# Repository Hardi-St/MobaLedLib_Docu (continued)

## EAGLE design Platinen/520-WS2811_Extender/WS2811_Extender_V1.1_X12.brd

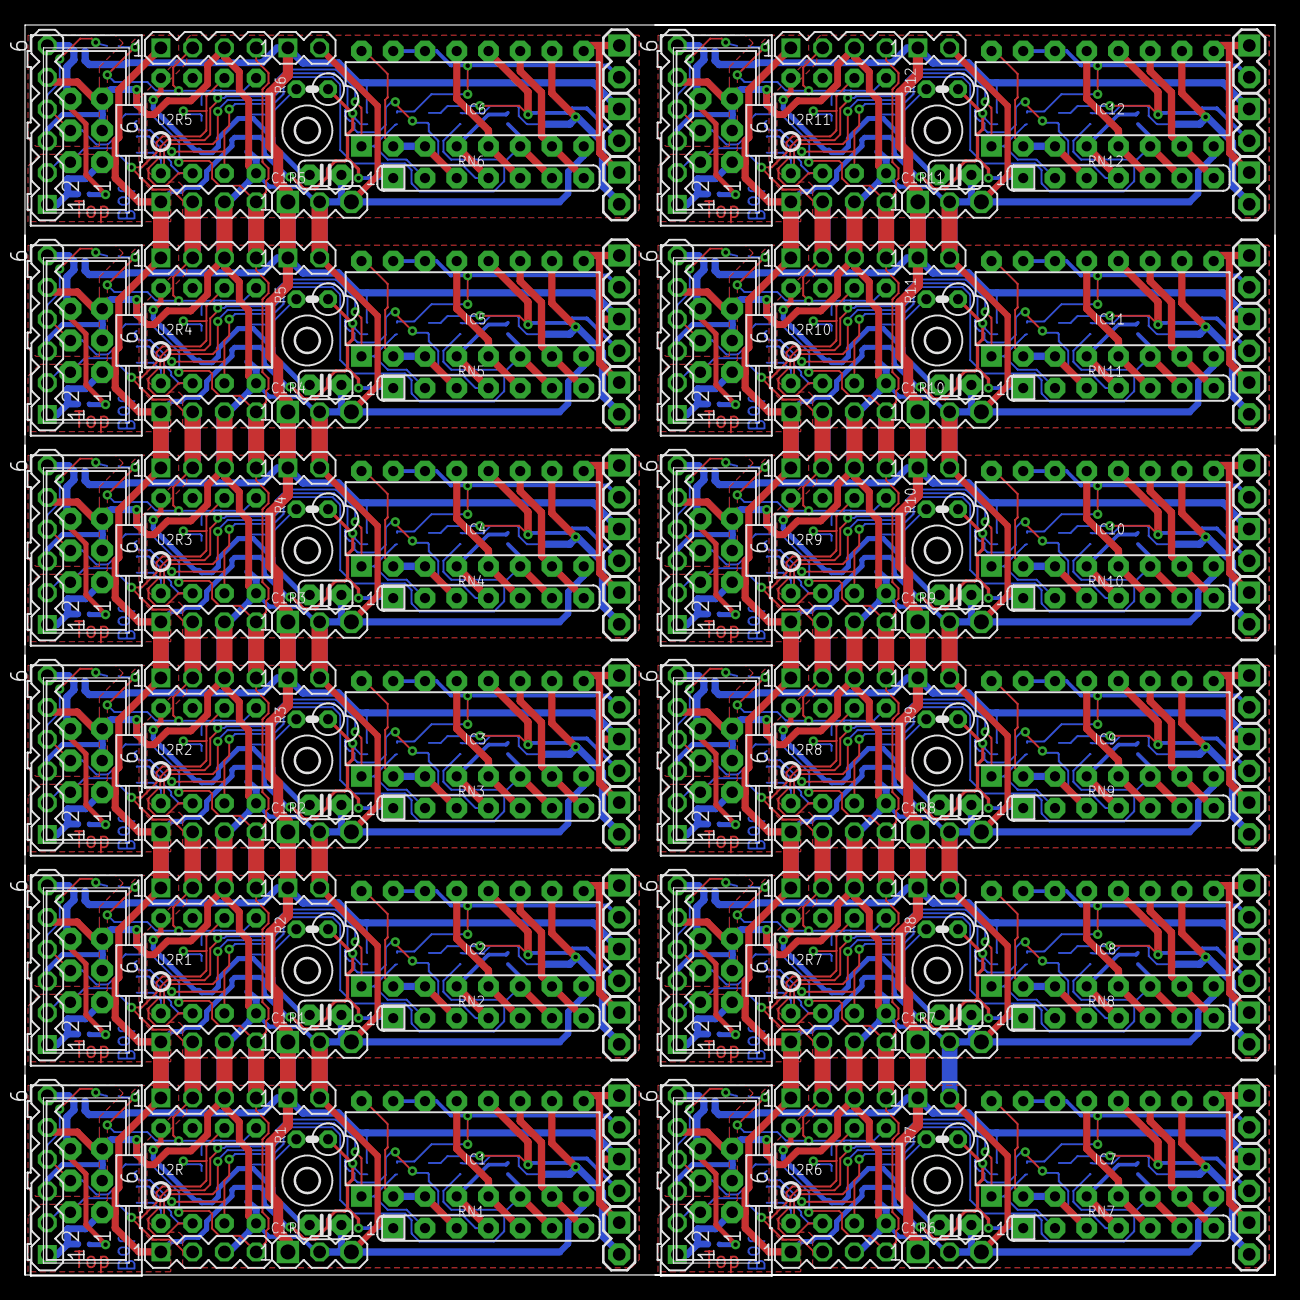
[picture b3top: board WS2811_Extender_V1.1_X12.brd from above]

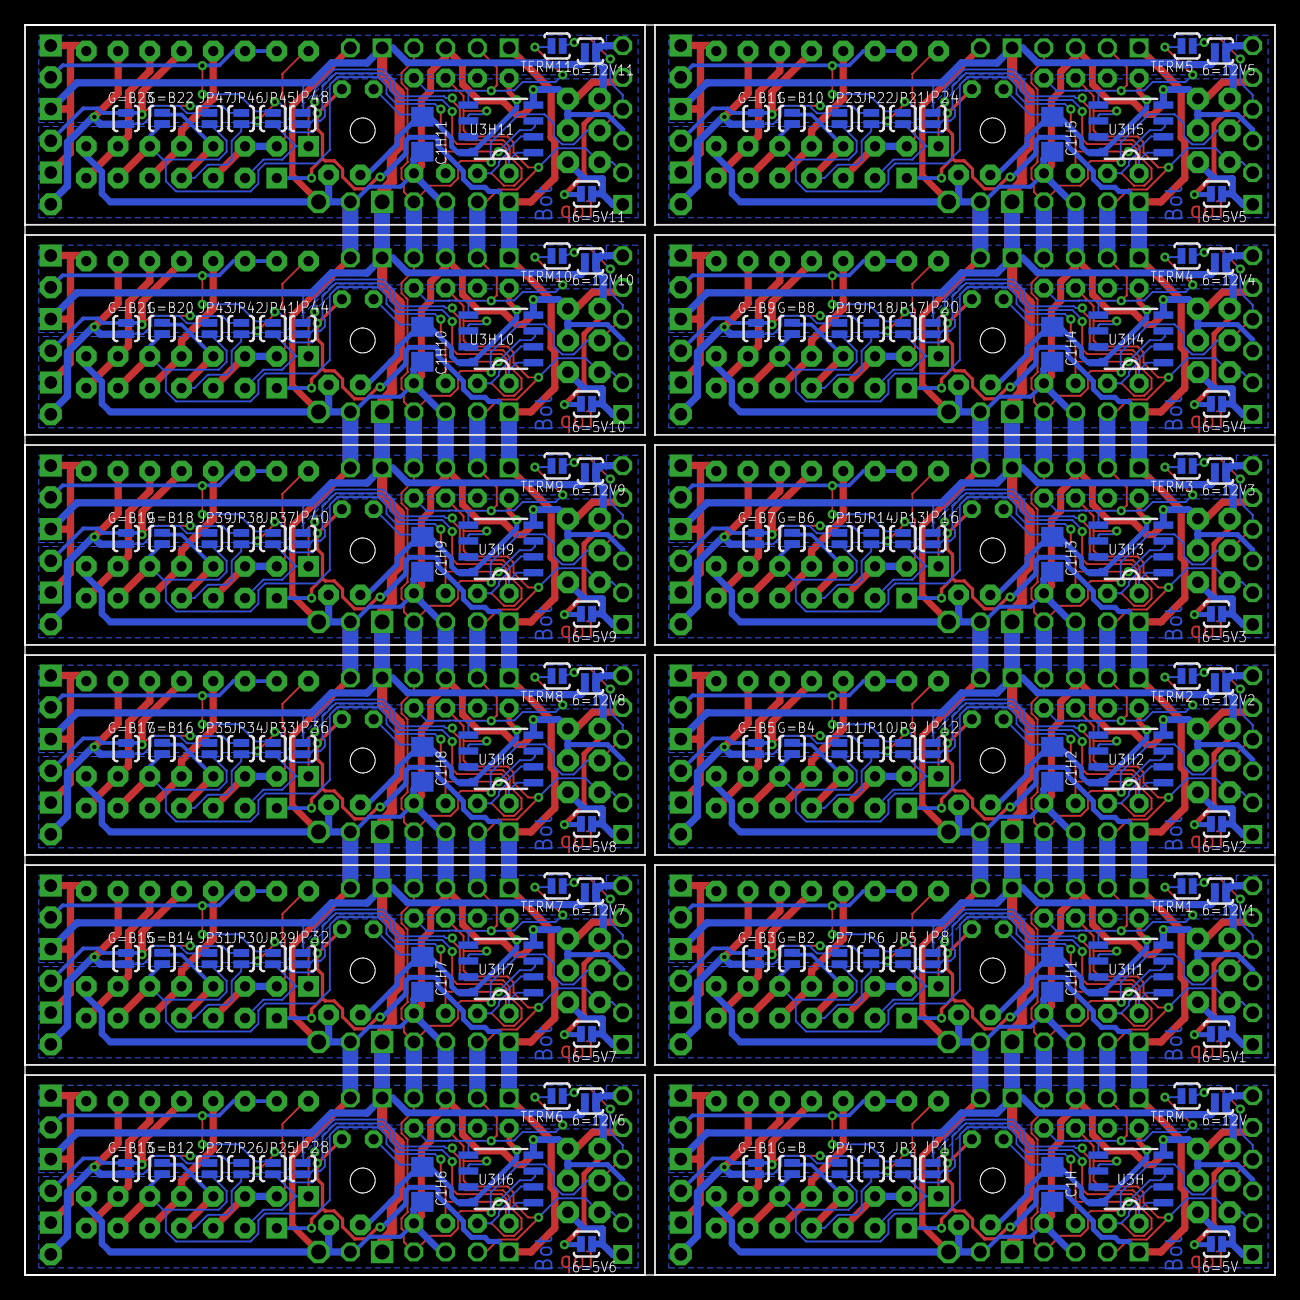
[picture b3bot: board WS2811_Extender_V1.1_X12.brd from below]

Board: 2 copper layers, 100.0 x 100.0 mm, 312 parts (132 on the bottom side), 204 nets.

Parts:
6=5V, 6=5V1, 6=5V2, 6=5V3, 6=5V4, 6=5V5, 6=5V6, 6=5V7, 6=5V8, 6=5V9, 6=5V10, 6=5V11, 6=12V, 6=12V1, 6=12V2, 6=12V3, 6=12V4, 6=12V5, 6=12V6, 6=12V7, 6=12V8, 6=12V9, 6=12V10, 6=12V11: SOLDERJUMPERNO; SJ_2S-NO
C1H, C1H1, C1H2, C1H3, C1H4, C1H5, C1H6, C1H7, C1H8, C1H9, C1H10, C1H11: 100n; C1206
C1R, C1R1, C1R2, C1R3, C1R4, C1R5, C1R6, C1R7, C1R8, C1R9, C1R10, C1R11: 100n; C025-024X044
G=B, G=B1, G=B2, G=B3, G=B4, G=B5, G=B6, G=B7, G=B8, G=B9, G=B10, G=B11, G=B12, G=B13, G=B14, G=B15, G=B16, G=B17, G=B18, G=B19, G=B20, G=B21, G=B22, G=B23: SOLDERJUMPERNO; SJ_2S-NO
H1, H2, H3, H4, H5, H6, H7, H8, H9, H10, H11, H12: MOUNT-HOLE2.0; 2,0
IC1, IC2, IC3, IC4, IC5, IC6, IC7, IC8, IC9, IC10, IC11, IC12: ULN2003AN; DIL16
J1, J5, J8, J11, J14, J17, J20, J23, J26, J29, J32, J35: Out2; 1X02
J2, J6, J9, J12, J15, J18, J21, J24, J27, J30, J33, J36: Out3; 1X02
J3, J4, J7, J10, J13, J16, J19, J22, J25, J28, J31, J34: Out1; 1X02
JP1, JP2, JP3, JP4, JP5, JP6, JP7, JP8, JP9, JP10, JP11, JP12, JP13, JP14, JP15, JP16, JP17, JP18, JP19, JP20, JP21, JP22, JP23, JP24, JP25, JP26, JP27, JP28, JP29, JP30, JP31, JP32, JP33, JP34, JP35, JP36, JP37, JP38, JP39, JP40, JP41, JP42, JP43, JP44, JP45, JP46, JP47, JP48: SOLDERJUMPERNO; SJ_2S-NO
O1, O2, O3, O4, O5, O6, O7, O8, O9, O10, O11, O12: ML6
R1, R2, R3, R4, R5, R6, R7, R8, R9, R10, R11, R12: 150; RCL_0207/2V
RN1, RN2, RN3, RN4, RN5, RN6, RN7, RN8, RN9, RN10, RN11, RN12: 1K; SIL7
SV1, SV8, SV13, SV18, SV23, SV28, SV33, SV38, SV43, SV48, SV53, SV58: MA02-1
SV2, SV10, SV15, SV20, SV25, SV30, SV35, SV40, SV45, SV50, SV55, SV60: MA06-1
SV3, SV4, SV5, SV7, SV11, SV12, SV16, SV17, SV21, SV22, SV26, SV27, SV31, SV32, SV36, SV37, SV41, SV42, SV46, SV47, SV51, SV52, SV56, SV57: MA04-1
SV6, SV9, SV14, SV19, SV24, SV29, SV34, SV39, SV44, SV49, SV54, SV59: MA03-1
TERM, TERM1, TERM2, TERM3, TERM4, TERM5, TERM6, TERM7, TERM8, TERM9, TERM10, TERM11: SOLDERJUMPERNO; SJ_2S-NO
U2R, U2R1, U2R2, U2R3, U2R4, U2R5, U2R6, U2R7, U2R8, U2R9, U2R10, U2R11: TINY45-20-DIP; S3PO_MODUL_WS2811_SOUND_MP3-TF-16P_WS2811_AND_ATTINY_WS2811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
U3H, U3H1, U3H2, U3H3, U3H4, U3H5, U3H6, U3H7, U3H8, U3H9, U3H10, U3H11: WS2811 SOT-8; SOP8

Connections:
12V: 6=12V.2, IC1.9, J1.1, J2.1, J4.1, JP1.2, SV1.1, SV6.1
12V1: 6=12V1.2, IC2.9, J3.1, J5.1, J6.1, JP8.2, SV8.1, SV9.1
12V2: 6=12V2.2, IC3.9, J7.1, J8.1, J9.1, JP12.2, SV13.1, SV14.1
12V3: 6=12V3.2, IC4.9, J10.1, J11.1, J12.1, JP16.2, SV18.1, SV19.1
12V4: 6=12V4.2, IC5.9, J13.1, J14.1, J15.1, JP20.2, SV23.1, SV24.1
12V5: 6=12V5.2, IC6.9, J16.1, J17.1, J18.1, JP24.2, SV28.1, SV29.1
12V6: 6=12V6.2, IC7.9, J19.1, J20.1, J21.1, JP28.2, SV33.1, SV34.1
12V7: 6=12V7.2, IC8.9, J22.1, J23.1, J24.1, JP32.2, SV38.1, SV39.1
12V8: 6=12V8.2, IC9.9, J25.1, J26.1, J27.1, JP36.2, SV43.1, SV44.1
12V9: 6=12V9.2, IC10.9, J28.1, J29.1, J30.1, JP40.2, SV48.1, SV49.1
12V10: 6=12V10.2, IC11.9, J31.1, J32.1, J33.1, JP44.2, SV53.1, SV54.1
12V11: 6=12V11.2, IC12.9, J34.1, J35.1, J36.1, JP48.2, SV58.1, SV59.1
+5V: 6=5V.2, JP1.1, O1.1, R1.1, RN1.1, SV2.1, SV3.1, SV4.1
+5V1: 6=5V1.2, JP8.1, O2.1, R2.1, RN2.1, SV5.1, SV7.1, SV10.1
+5V2: 6=5V2.2, JP12.1, O3.1, R3.1, RN3.1, SV11.1, SV12.1, SV15.1
+5V3: 6=5V3.2, JP16.1, O4.1, R4.1, RN4.1, SV16.1, SV17.1, SV20.1
+5V4: 6=5V4.2, JP20.1, O5.1, R5.1, RN5.1, SV21.1, SV22.1, SV25.1
+5V5: 6=5V5.2, JP24.1, O6.1, R6.1, RN6.1, SV26.1, SV27.1, SV30.1
+5V6: 6=5V6.2, JP28.1, O7.1, R7.1, RN7.1, SV31.1, SV32.1, SV35.1
+5V7: 6=5V7.2, JP32.1, O8.1, R8.1, RN8.1, SV36.1, SV37.1, SV40.1
+5V8: 6=5V8.2, JP36.1, O9.1, R9.1, RN9.1, SV41.1, SV42.1, SV45.1
+5V9: 6=5V9.2, JP40.1, O10.1, R10.1, RN10.1, SV46.1, SV47.1, SV50.1
+5V10: 6=5V10.2, JP44.1, O11.1, R11.1, RN11.1, SV51.1, SV52.1, SV55.1
+5V11: 6=5V11.2, JP48.1, O12.1, R12.1, RN12.1, SV56.1, SV57.1, SV60.1
GND: C1H.2, C1R.2, IC1.8, O1.3, O1.5, SV1.2, SV2.3, SV2.5, SV3.3, SV4.3, SV6.2, SV6.3, U2R.4, U3H.4
GND1: C1H1.2, C1R1.2, IC2.8, O2.3, O2.5, SV5.3, SV7.3, SV8.2, SV9.2, SV9.3, SV10.3, SV10.5, U2R1.4, U3H1.4
GND2: C1H2.2, C1R2.2, IC3.8, O3.3, O3.5, SV11.3, SV12.3, SV13.2, SV14.2, SV14.3, SV15.3, SV15.5, U2R2.4, U3H2.4
GND3: C1H3.2, C1R3.2, IC4.8, O4.3, O4.5, SV16.3, SV17.3, SV18.2, SV19.2, SV19.3, SV20.3, SV20.5, U2R3.4, U3H3.4
GND4: C1H4.2, C1R4.2, IC5.8, O5.3, O5.5, SV21.3, SV22.3, SV23.2, SV24.2, SV24.3, SV25.3, SV25.5, U2R4.4, U3H4.4
GND5: C1H5.2, C1R5.2, IC6.8, O6.3, O6.5, SV26.3, SV27.3, SV28.2, SV29.2, SV29.3, SV30.3, SV30.5, U2R5.4, U3H5.4
GND6: C1H6.2, C1R6.2, IC7.8, O7.3, O7.5, SV31.3, SV32.3, SV33.2, SV34.2, SV34.3, SV35.3, SV35.5, U2R6.4, U3H6.4
GND7: C1H7.2, C1R7.2, IC8.8, O8.3, O8.5, SV36.3, SV37.3, SV38.2, SV39.2, SV39.3, SV40.3, SV40.5, U2R7.4, U3H7.4
GND8: C1H8.2, C1R8.2, IC9.8, O9.3, O9.5, SV41.3, SV42.3, SV43.2, SV44.2, SV44.3, SV45.3, SV45.5, U2R8.4, U3H8.4
GND9: C1H9.2, C1R9.2, IC10.8, O10.3, O10.5, SV46.3, SV47.3, SV48.2, SV49.2, SV49.3, SV50.3, SV50.5, U2R9.4, U3H9.4
GND10: C1H10.2, C1R10.2, IC11.8, O11.3, O11.5, SV51.3, SV52.3, SV53.2, SV54.2, SV54.3, SV55.3, SV55.5, U2R10.4, U3H10.4
GND11: C1H11.2, C1R11.2, IC12.8, O12.3, O12.5, SV56.3, SV57.3, SV58.2, SV59.2, SV59.3, SV60.3, SV60.5, U2R11.4, U3H11.4
unnamed: O1.2, SV2.2, SV4.2, U2R.6, U3H.6
unnamed: SV3.2, TERM.2, U2R.5, U3H.5
unnamed: O1.4, SV2.4, SV3.4, SV4.4, TERM.1
unnamed: C1H.1, C1R.1, R1.2, U2R.8, U3H.8
unnamed: IC1.1, JP2.1, RN1.2, U2R.2, U3H.2
unnamed: 6=5V.1, 6=12V.1, O1.6, SV2.6
unnamed: O2.2, SV7.2, SV10.2, U2R1.6, U3H1.6
unnamed: G=B.2, IC1.6, JP4.1, RN1.6, U2R.3, U3H.3
unnamed: IC1.2, IC1.3, IC1.16, RN1.3
unnamed: SV5.2, TERM1.2, U2R1.5, U3H1.5
unnamed: IC1.5, IC1.13, RN1.5
unnamed: IC1.7, IC1.11, RN1.7
unnamed: O2.4, SV5.4, SV7.4, SV10.4, TERM1.1
unnamed: C1H1.1, C1R1.1, R2.2, U2R1.8, U3H1.8
unnamed: 6=5V1.1, 6=12V1.1, O2.6, SV10.6
unnamed: IC2.1, JP5.1, RN2.2, U2R1.2, U3H1.2
unnamed: G=B2.2, IC2.6, JP7.1, RN2.6, U2R1.3, U3H1.3
unnamed: G=B2.1, IC2.4, JP6.1, RN2.4, U2R1.1, U3H1.1
unnamed: IC2.2, IC2.3, IC2.16, RN2.3
unnamed: IC2.5, IC2.13, RN2.5
unnamed: G=B.1, IC1.4, JP3.1, RN1.4, U2R.1, U3H.1
unnamed: IC2.7, IC2.11, RN2.7
unnamed: O3.2, SV12.2, SV15.2, U2R2.6, U3H2.6
unnamed: SV11.2, TERM2.2, U2R2.5, U3H2.5
unnamed: O3.4, SV11.4, SV12.4, SV15.4, TERM2.1
unnamed: C1H2.1, C1R2.1, R3.2, U2R2.8, U3H2.8
unnamed: 6=5V2.1, 6=12V2.1, O3.6, SV15.6
unnamed: IC3.1, JP9.1, RN3.2, U2R2.2, U3H2.2
unnamed: G=B4.2, IC3.6, JP11.1, RN3.6, U2R2.3, U3H2.3
unnamed: G=B4.1, IC3.4, JP10.1, RN3.4, U2R2.1, U3H2.1
unnamed: IC3.2, IC3.3, IC3.16, RN3.3
unnamed: IC3.5, IC3.13, RN3.5
unnamed: IC3.7, IC3.11, RN3.7
unnamed: O4.2, SV17.2, SV20.2, U2R3.6, U3H3.6
unnamed: SV16.2, TERM3.2, U2R3.5, U3H3.5
unnamed: O4.4, SV16.4, SV17.4, SV20.4, TERM3.1
unnamed: C1H3.1, C1R3.1, R4.2, U2R3.8, U3H3.8
unnamed: 6=5V3.1, 6=12V3.1, O4.6, SV20.6
unnamed: IC4.1, JP13.1, RN4.2, U2R3.2, U3H3.2
unnamed: G=B6.2, IC4.6, JP15.1, RN4.6, U2R3.3, U3H3.3
unnamed: G=B6.1, IC4.4, JP14.1, RN4.4, U2R3.1, U3H3.1
unnamed: IC4.2, IC4.3, IC4.16, RN4.3
unnamed: IC4.5, IC4.13, RN4.5
unnamed: IC4.7, IC4.11, RN4.7
unnamed: O5.2, SV22.2, SV25.2, U2R4.6, U3H4.6
unnamed: SV21.2, TERM4.2, U2R4.5, U3H4.5
unnamed: O5.4, SV21.4, SV22.4, SV25.4, TERM4.1
unnamed: C1H4.1, C1R4.1, R5.2, U2R4.8, U3H4.8
unnamed: 6=5V4.1, 6=12V4.1, O5.6, SV25.6
unnamed: IC5.1, JP17.1, RN5.2, U2R4.2, U3H4.2
unnamed: G=B8.2, IC5.6, JP19.1, RN5.6, U2R4.3, U3H4.3
unnamed: G=B8.1, IC5.4, JP18.1, RN5.4, U2R4.1, U3H4.1
unnamed: IC5.2, IC5.3, IC5.16, RN5.3
unnamed: IC5.5, IC5.13, RN5.5
unnamed: IC5.7, IC5.11, RN5.7
unnamed: O6.2, SV27.2, SV30.2, U2R5.6, U3H5.6
unnamed: SV26.2, TERM5.2, U2R5.5, U3H5.5
unnamed: O6.4, SV26.4, SV27.4, SV30.4, TERM5.1
unnamed: C1H5.1, C1R5.1, R6.2, U2R5.8, U3H5.8
unnamed: 6=5V5.1, 6=12V5.1, O6.6, SV30.6
unnamed: IC6.1, JP21.1, RN6.2, U2R5.2, U3H5.2
unnamed: G=B10.2, IC6.6, JP23.1, RN6.6, U2R5.3, U3H5.3
unnamed: G=B10.1, IC6.4, JP22.1, RN6.4, U2R5.1, U3H5.1
unnamed: IC6.2, IC6.3, IC6.16, RN6.3
unnamed: IC6.5, IC6.13, RN6.5
unnamed: IC6.7, IC6.11, RN6.7
unnamed: O7.2, SV32.2, SV35.2, U2R6.6, U3H6.6
unnamed: SV31.2, TERM6.2, U2R6.5, U3H6.5
unnamed: O7.4, SV31.4, SV32.4, SV35.4, TERM6.1
unnamed: C1H6.1, C1R6.1, R7.2, U2R6.8, U3H6.8
unnamed: 6=5V6.1, 6=12V6.1, O7.6, SV35.6
unnamed: IC7.1, JP25.1, RN7.2, U2R6.2, U3H6.2
unnamed: G=B12.2, IC7.6, JP27.1, RN7.6, U2R6.3, U3H6.3
unnamed: G=B12.1, IC7.4, JP26.1, RN7.4, U2R6.1, U3H6.1
unnamed: IC7.2, IC7.3, IC7.16, RN7.3
unnamed: IC7.5, IC7.13, RN7.5
unnamed: IC7.7, IC7.11, RN7.7
unnamed: O8.2, SV37.2, SV40.2, U2R7.6, U3H7.6
unnamed: SV36.2, TERM7.2, U2R7.5, U3H7.5
unnamed: O8.4, SV36.4, SV37.4, SV40.4, TERM7.1
unnamed: C1H7.1, C1R7.1, R8.2, U2R7.8, U3H7.8
unnamed: 6=5V7.1, 6=12V7.1, O8.6, SV40.6
unnamed: IC8.1, JP29.1, RN8.2, U2R7.2, U3H7.2
unnamed: G=B14.2, IC8.6, JP31.1, RN8.6, U2R7.3, U3H7.3
unnamed: G=B14.1, IC8.4, JP30.1, RN8.4, U2R7.1, U3H7.1
unnamed: IC8.2, IC8.3, IC8.16, RN8.3
unnamed: IC8.5, IC8.13, RN8.5
unnamed: IC8.7, IC8.11, RN8.7
unnamed: O9.2, SV42.2, SV45.2, U2R8.6, U3H8.6
unnamed: SV41.2, TERM8.2, U2R8.5, U3H8.5
unnamed: O9.4, SV41.4, SV42.4, SV45.4, TERM8.1
unnamed: C1H8.1, C1R8.1, R9.2, U2R8.8, U3H8.8
unnamed: 6=5V8.1, 6=12V8.1, O9.6, SV45.6
unnamed: IC9.1, JP33.1, RN9.2, U2R8.2, U3H8.2
unnamed: G=B16.2, IC9.6, JP35.1, RN9.6, U2R8.3, U3H8.3
unnamed: G=B16.1, IC9.4, JP34.1, RN9.4, U2R8.1, U3H8.1
unnamed: IC9.2, IC9.3, IC9.16, RN9.3
unnamed: IC9.5, IC9.13, RN9.5
unnamed: IC9.7, IC9.11, RN9.7
unnamed: O10.2, SV47.2, SV50.2, U2R9.6, U3H9.6
unnamed: SV46.2, TERM9.2, U2R9.5, U3H9.5
unnamed: O10.4, SV46.4, SV47.4, SV50.4, TERM9.1
unnamed: C1H9.1, C1R9.1, R10.2, U2R9.8, U3H9.8
unnamed: 6=5V9.1, 6=12V9.1, O10.6, SV50.6
unnamed: IC10.1, JP37.1, RN10.2, U2R9.2, U3H9.2
unnamed: G=B18.2, IC10.6, JP39.1, RN10.6, U2R9.3, U3H9.3
unnamed: G=B18.1, IC10.4, JP38.1, RN10.4, U2R9.1, U3H9.1
unnamed: IC10.2, IC10.3, IC10.16, RN10.3
unnamed: IC10.5, IC10.13, RN10.5
unnamed: IC10.7, IC10.11, RN10.7
unnamed: O11.2, SV52.2, SV55.2, U2R10.6, U3H10.6
unnamed: SV51.2, TERM10.2, U2R10.5, U3H10.5
unnamed: O11.4, SV51.4, SV52.4, SV55.4, TERM10.1
unnamed: C1H10.1, C1R10.1, R11.2, U2R10.8, U3H10.8
unnamed: 6=5V10.1, 6=12V10.1, O11.6, SV55.6
unnamed: IC11.1, JP41.1, RN11.2, U2R10.2, U3H10.2
unnamed: G=B20.2, IC11.6, JP43.1, RN11.6, U2R10.3, U3H10.3
unnamed: G=B20.1, IC11.4, JP42.1, RN11.4, U2R10.1, U3H10.1
unnamed: IC11.2, IC11.3, IC11.16, RN11.3
unnamed: IC11.5, IC11.13, RN11.5
unnamed: IC11.7, IC11.11, RN11.7
unnamed: O12.2, SV57.2, SV60.2, U2R11.6, U3H11.6
unnamed: SV56.2, TERM11.2, U2R11.5, U3H11.5
unnamed: O12.4, SV56.4, SV57.4, SV60.4, TERM11.1
unnamed: C1H11.1, C1R11.1, R12.2, U2R11.8, U3H11.8
unnamed: 6=5V11.1, 6=12V11.1, O12.6, SV60.6
unnamed: IC12.1, JP45.1, RN12.2, U2R11.2, U3H11.2
unnamed: G=B22.2, IC12.6, JP47.1, RN12.6, U2R11.3, U3H11.3
unnamed: G=B22.1, IC12.4, JP46.1, RN12.4, U2R11.1, U3H11.1
unnamed: IC12.2, IC12.3, IC12.16, RN12.3
unnamed: IC12.5, IC12.13, RN12.5
unnamed: IC12.7, IC12.11, RN12.7
O1: IC1.14, IC1.15, J4.2, JP2.2
O2: G=B1.2, IC1.12, J1.2, JP3.2
O3: G=B1.1, IC1.10, J2.2, JP4.2
O4: IC2.14, IC2.15, J3.2, JP5.2
O5: G=B3.1, IC2.10, J6.2, JP7.2
O6: G=B3.2, IC2.12, J5.2, JP6.2
O7: IC3.14, IC3.15, J7.2, JP9.2
O8: G=B5.1, IC3.10, J9.2, JP11.2
O9: G=B5.2, IC3.12, J8.2, JP10.2
O10: IC4.14, IC4.15, J10.2, JP13.2
O11: G=B7.1, IC4.10, J12.2, JP15.2
O12: G=B7.2, IC4.12, J11.2, JP14.2
O13: IC5.14, IC5.15, J13.2, JP17.2
O14: G=B9.1, IC5.10, J15.2, JP19.2
O15: G=B9.2, IC5.12, J14.2, JP18.2
O16: IC6.14, IC6.15, J16.2, JP21.2
O17: G=B11.1, IC6.10, J18.2, JP23.2
O18: G=B11.2, IC6.12, J17.2, JP22.2
O19: IC7.14, IC7.15, J19.2, JP25.2
O20: G=B13.1, IC7.10, J21.2, JP27.2
O21: G=B13.2, IC7.12, J20.2, JP26.2
O22: IC8.14, IC8.15, J22.2, JP29.2
O23: G=B15.1, IC8.10, J24.2, JP31.2
O24: G=B15.2, IC8.12, J23.2, JP30.2
O25: IC9.14, IC9.15, J25.2, JP33.2
O26: G=B17.1, IC9.10, J27.2, JP35.2
O27: G=B17.2, IC9.12, J26.2, JP34.2
O28: IC10.14, IC10.15, J28.2, JP37.2
O29: G=B19.1, IC10.10, J30.2, JP39.2
O30: G=B19.2, IC10.12, J29.2, JP38.2
O31: IC11.14, IC11.15, J31.2, JP41.2
O32: G=B21.1, IC11.10, J33.2, JP43.2
O33: G=B21.2, IC11.12, J32.2, JP42.2
O34: IC12.14, IC12.15, J34.2, JP45.2
O35: G=B23.1, IC12.10, J36.2, JP47.2
O36: G=B23.2, IC12.12, J35.2, JP46.2

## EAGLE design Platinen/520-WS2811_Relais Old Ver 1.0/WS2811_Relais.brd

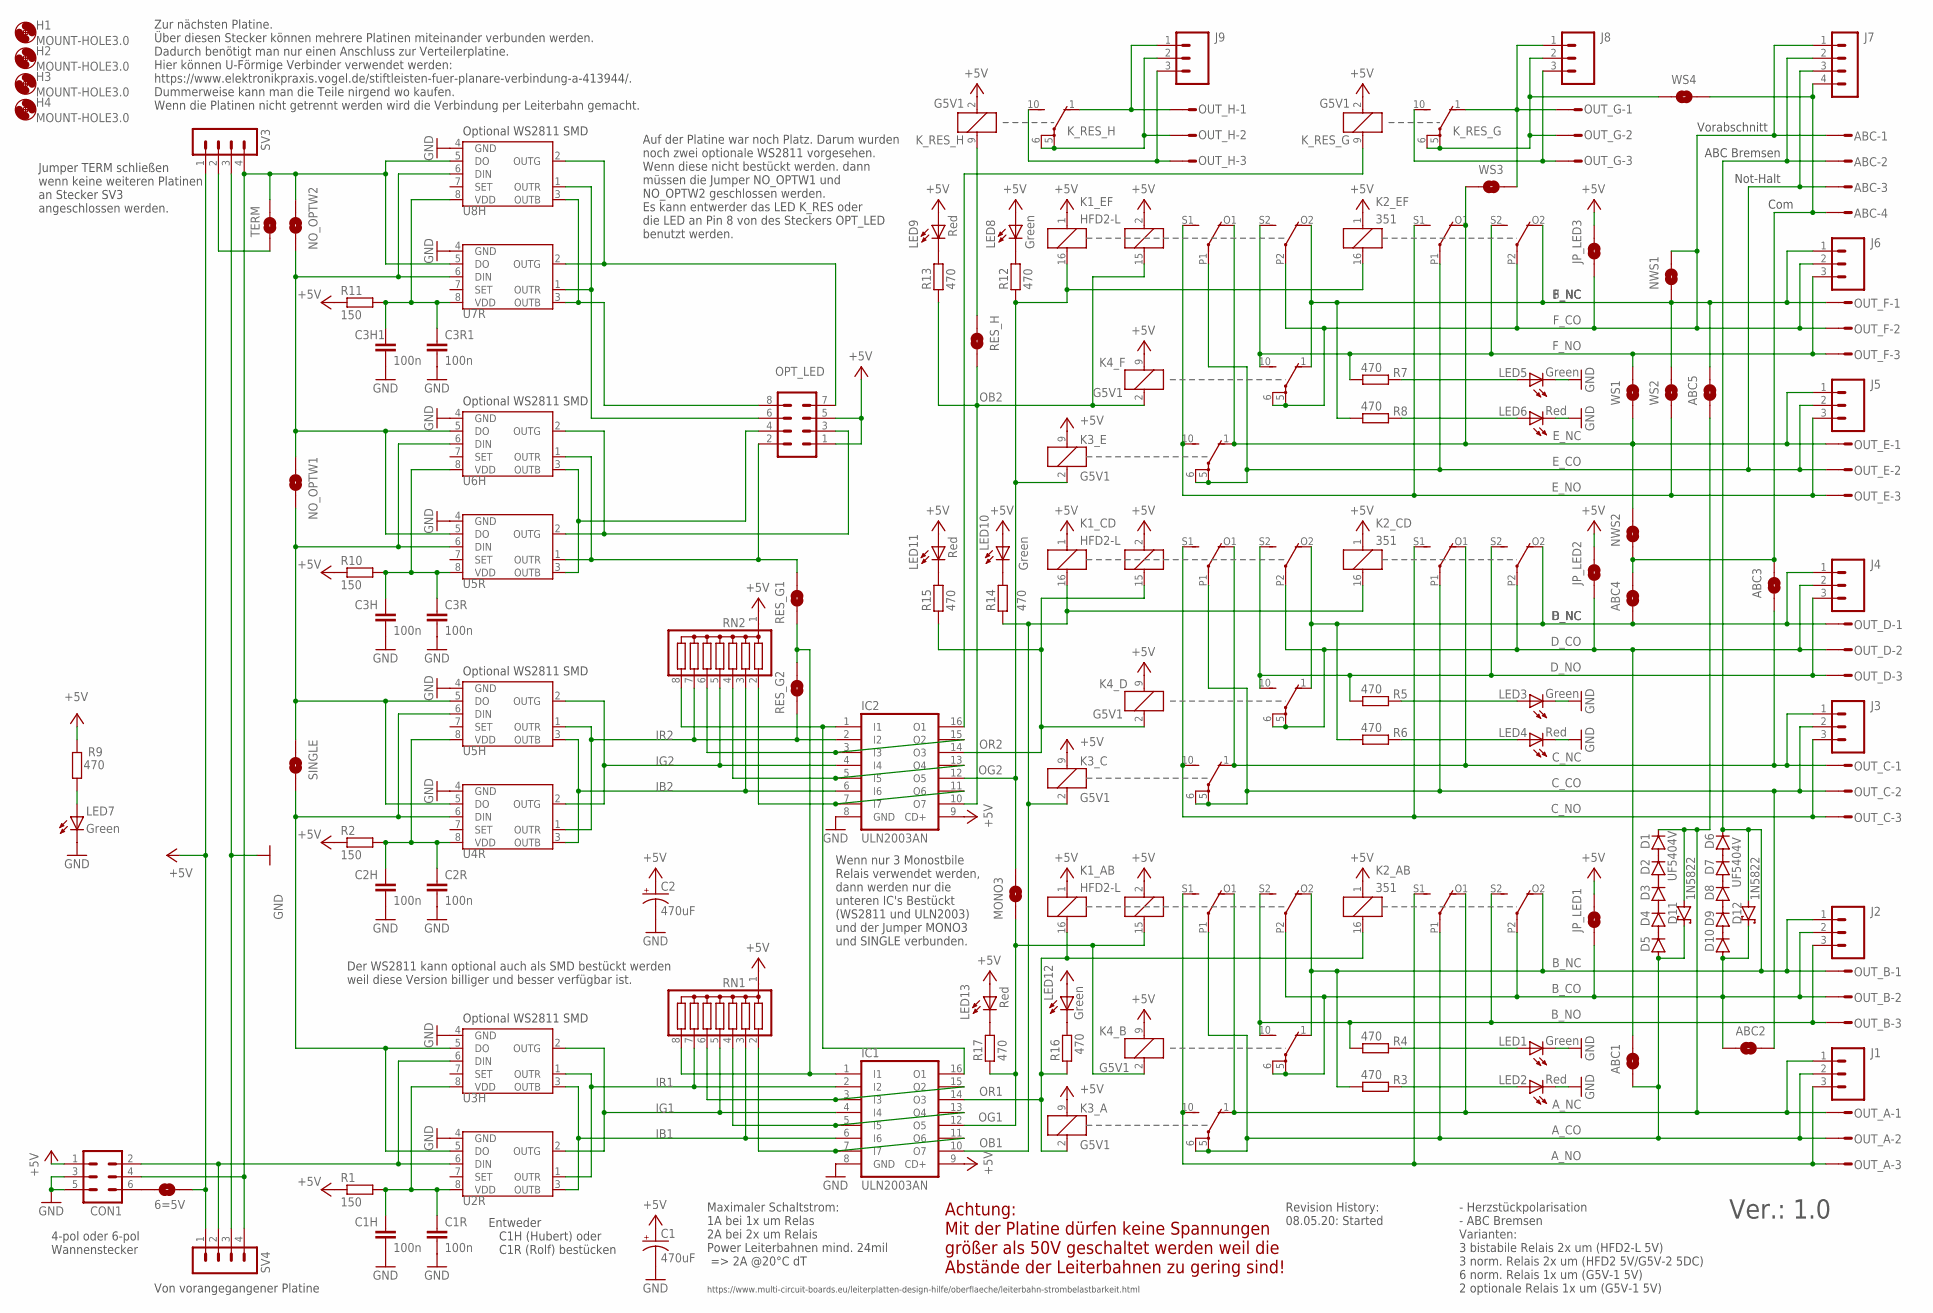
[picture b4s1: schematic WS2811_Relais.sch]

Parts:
6=5V: SOLDERJUMPERNO; SJ_2S-NO
ABC: STL1550-4ON_BOARD; STL1550-4_ON_BOARD
ABC1, ABC2, ABC3, ABC4, ABC5: SOLDERJUMPERNO; SJ_2S-NO
C1, C2: 470uF; SPARKFUN-CAPACITORS_CPOL-RADIAL-100UF-25V
C1H, C2H, C3H, C3H1: 100n; C1206
C1R, C2R, C3R, C3R1: 100n; C025-024X044
CON1: ML6
D1, D2, D3, D4, D5, D6, D7, D8, D9, D10: UF5404V; DO201-15-V
D11, D12: 1N5822; DO41-7.6
H1, H2, H3, H4: MOUNT-HOLE3.0; 3,0
IC1, IC2: ULN2003AN; DIL16
J1, J2, J3, J4, J5, J6, J8, J9: M03PTH; 1X03
J7: MA04-1
JP_LED1, JP_LED2, JP_LED3: SOLDERJUMPERNO; SJ_2S-NO
K1_AB, K1_CD, K1_EF: HFD2-L
K2_AB, K2_CD, K2_EF: 351
K3_A, K3_C, K3_E, K4_B, K4_D, K4_F: G5V1
K_RES_G: G5V1
K_RES_H: G5V1
LED1, LED3, LED5, LED7, LED8, LED10, LED12: Green; LED3MM
LED2, LED4, LED6, LED9, LED11, LED13: Red; LED3MM
MONO3: SOLDERJUMPERNO; SJ_2S-NO
NO_OPTW1, NO_OPTW2: SOLDERJUMPERNO; SJ_2S-NO
NWS1, NWS2: SOLDERJUMPERNO; SJ_2S-NO
OPT_LED: CON-HARTING-ML_ML08
OUT_A: STL1550-3; STL1550-3_ON_BOARD
OUT_B: STL1550-3; STL1550-3_ON_BOARD
OUT_C: STL1550-3; STL1550-3_ON_BOARD
OUT_D: STL1550-3; STL1550-3_ON_BOARD
OUT_E: STL1550-3; STL1550-3_ON_BOARD
OUT_F: STL1550-3; STL1550-3_ON_BOARD
OUT_G: STL1550-3; STL1550-3_ON_BOARD
OUT_H: STL1550-3; STL1550-3_ON_BOARD
R1, R2, R10, R11: 150; RCL_0207/2V
R3, R4, R5, R6, R7, R8, R9, R12, R13, R14, R15, R16, R17: 470; 0204/2V
RES_G1, RES_G2: SOLDERJUMPERNO; SJ_2S-NO
RES_H: SOLDERJUMPERNO; SJ_2S-NO
RN1, RN2: G07R; SIL8
SINGLE: SOLDERJUMPERNO; SJ_2S-NO
SV3, SV4: MA04-1
TERM: SOLDERJUMPERNO; SJ_2S-NO
U2R, U4R, U5R, U7R: WS2811; S3PO_MODUL_WS2811_SOUND_MP3-TF-16P_WS2811_AND_ATTINY_WS2811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
U3H, U5H, U6H, U8H: WS2811 SOT-8; SOP8
WS1, WS2, WS3, WS4: SOLDERJUMPERNO; SJ_2S-NO

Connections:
$N100: IC2.7 (I7), IC2.11 (O6), RN2.2
+5V: 6=5V.2, C1.1 (+), C2.1 (+), CON1.1, IC1.9 (CD+), IC2.9 (CD+), JP_LED1.2, JP_LED2.2, JP_LED3.2, K1_AB.1, K1_AB.2 (3), K1_CD.1, K1_CD.2 (3), K1_EF.1, K1_EF.2 (3), K2_AB.1, K2_CD.1, K2_EF.1, K3_A.9 (2), K3_C.9 (2), K3_E.9 (2), K4_B.9 (2), K4_D.9 (2), K4_F.9 (2), K_RES_G.2 (1), K_RES_H.2 (1), LED8.A, LED9.A, LED10.A, LED11.A, LED12.A, LED13.A, OPT_LED.1, OPT_LED.5, R1.1, R2.1, R9.1, R10.1, R11.1, RN1.1, RN2.1, SV3.1, SV4.1
A_CO: ABC1.1, D5.A, D11.C, J1.2, K1_AB.P1, K2_AB.P1, K3_A.5, K3_A.6, OUT_A.2
A_NC: ABC5.2, D1.C, D11.A, J1.1, K1_AB.O1 (O), K2_AB.O1 (O), K3_A.1 (O), OUT_A.1
A_NO: J1.3, K1_AB.S1 (S), K2_AB.S1 (S), K3_A.10 (S), OUT_A.3
B_CO: ABC2.1, D10.A, D12.C, J2.2, JP_LED1.1, K1_AB.P2, K2_AB.P2, K4_B.5, K4_B.6, OUT_B.2
B_NC: ABC.2, D6.C, D12.A, J2.1, J7.2, K1_AB.O2 (O), K2_AB.O2 (O), K4_B.1 (O), OUT_B.1, R3.2
B_NO: J2.3, K1_AB.S2 (S), K2_AB.S2 (S), K4_B.10 (S), OUT_B.3, R4.2
C_CO: ABC2.2, J3.2, K1_CD.P1, K2_CD.P1, K3_C.5, K3_C.6, OUT_C.2
C_NC: ABC3.2, J3.1, K1_CD.O1 (O), K2_CD.O1 (O), K3_C.1 (O), OUT_C.1
C_NO: J3.3, K1_CD.S1 (S), K2_CD.S1 (S), K3_C.10 (S), OUT_C.3
D_CO: ABC1.2, J4.2, JP_LED2.1, K1_CD.P2, K2_CD.P2, K4_D.5, K4_D.6, OUT_D.2
D_NC: ABC4.2, J4.1, K1_CD.O2 (O), K2_CD.O2 (O), K4_D.1 (O), OUT_D.1, R6.2
D_NO: J4.3, K1_CD.S2 (S), K2_CD.S2 (S), K4_D.10 (S), OUT_D.3, R5.2
E_CO: ABC.3, J5.2, J7.3, K1_EF.P1, K2_EF.P1, K3_E.5, K3_E.6, OUT_E.2
E_NC: J5.1, K1_EF.O1 (O), K2_EF.O1 (O), K3_E.1 (O), NWS2.1, OUT_E.1, WS1.2, WS3.2
E_NO: J5.3, K1_EF.S1 (S), K2_EF.S1 (S), K3_E.10 (S), OUT_E.3, WS2.2
F_CO: ABC.1, J6.2, J7.1, JP_LED3.1, K1_EF.P2, K2_EF.P2, K4_F.5, K4_F.6, NWS1.1, OUT_F.2
F_NC: ABC5.1, J6.1, K1_EF.O2 (O), K2_EF.O2 (O), K4_F.1 (O), NWS1.2, OUT_F.1, R8.2, WS2.1
F_NO: J6.3, K1_EF.S2 (S), K2_EF.S2 (S), K4_F.10 (S), OUT_F.3, R7.2, WS1.1
GND: C1.2 (-), C1H.2, C1R.2, C2.2 (-), C2H.2, C2R.2, C3H.2, C3H1.2, C3R.2, C3R1.2, CON1.3, CON1.5, IC1.8 (GND), IC2.8 (GND), LED1.K (C), LED2.K (C), LED3.K (C), LED4.K (C), LED5.K (C), LED6.K (C), LED7.K (C), SV3.3, SV4.3, U2R.4 (GND), U3H.4 (GND), U4R.4 (GND), U5H.4 (GND), U5R.4 (GND), U6H.4 (GND), U7R.4 (GND), U8H.4 (GND)
IB1: IC1.6 (I6), RN1.3, U2R.3 (OUTB), U3H.3 (OUTB)
IB2: IC2.6 (I6), RN2.3, U4R.3 (OUTB), U5H.3 (OUTB)
IB3: OPT_LED.4, U5R.3 (OUTB), U6H.3 (OUTB)
IB4: OPT_LED.8, U7R.3 (OUTB), U8H.3 (OUTB)
IG1: IC1.4 (I4), RN1.5, U2R.2 (OUTG), U3H.2 (OUTG)
IG2: IC2.4 (I4), RN2.5, U4R.2 (OUTG), U5H.2 (OUTG)
IG3: OPT_LED.3, U5R.2 (OUTG), U6H.2 (OUTG)
IG4: OPT_LED.7, U7R.2 (OUTG), U8H.2 (OUTG)
IR1: IC1.2 (I2), RN1.7, U2R.1 (OUTR), U3H.1 (OUTR)
IR2: IC2.2 (I2), RES_G2.2, RN2.7, U4R.1 (OUTR), U5H.1 (OUTR)
IR3: IC1.1 (I1), RES_G1.2, RES_G2.1, RN1.8
IR4: OPT_LED.6, U7R.1 (OUTR), U8H.1 (OUTR)
unnamed: CON1.2, SV4.2, U2R.6 (DIN), U3H.6 (DIN)
unnamed: LED2.A, R3.1
unnamed: CON1.4, NO_OPTW2.1, SV3.4, SV4.4, TERM.1, U7R.5 (DO), U8H.5 (DO)
unnamed: C1H.1, C1R.1, R1.2, U2R.8 (VDD), U3H.8 (VDD)
unnamed: LED1.A, R4.1
unnamed: 6=5V.1, CON1.6
unnamed: IC1.7 (I7), IC1.11 (O6), RN1.2
unnamed: LED4.A, R6.1
unnamed: IC1.3 (I3), IC1.15 (O2), RN1.6
unnamed: SV3.2, TERM.2
unnamed: IC1.5 (I5), IC1.13 (O4), RN1.4
unnamed: LED3.A, R5.1
unnamed: C2H.1, C2R.1, R2.2, U4R.8 (VDD), U5H.8 (VDD)
unnamed: LED6.A, R8.1
unnamed: LED5.A, R7.1
unnamed: D1.A, D2.C
unnamed: IC1.16 (O1), IC2.1 (I1), RN2.8
unnamed: IC2.5 (I5), IC2.13 (O4), RN2.4
unnamed: D2.A, D3.C
unnamed: SINGLE.2, U2R.5 (DO), U3H.5 (DO), U4R.6 (DIN), U5H.6 (DIN)
unnamed: D3.A, D4.C
unnamed: LED7.A, R9.2
unnamed: D4.A, D5.C
unnamed: D7.A, D8.C
unnamed: D8.A, D9.C
unnamed: D9.A, D10.C
unnamed: D6.A, D7.C
unnamed: OPT_LED.2, RES_G1.1, U5R.1 (OUTR), U6H.1 (OUTR)
unnamed: IC2.3 (I3), IC2.15 (O2), RN2.6
unnamed: J8.2, K_RES_G.5, K_RES_G.6, OUT_G.2, WS4.2
unnamed: IC2.16 (O1), K_RES_G.9 (2)
unnamed: J8.1, K_RES_G.1 (O), OUT_G.1, WS3.1
unnamed: J8.3, K_RES_G.10 (S), OUT_G.3
unnamed: NO_OPTW1.1, NO_OPTW2.2, U5R.5 (DO), U6H.5 (DO), U7R.6 (DIN), U8H.6 (DIN)
unnamed: C3H.1, C3R.1, R10.2, U5R.8 (VDD), U6H.8 (VDD)
unnamed: J9.2, K_RES_H.5, K_RES_H.6, OUT_H.2
unnamed: NO_OPTW1.2, SINGLE.1, U4R.5 (DO), U5H.5 (DO), U5R.6 (DIN), U6H.6 (DIN)
unnamed: J9.3, K_RES_H.10 (S), OUT_H.3
unnamed: C3H1.1, C3R1.1, R11.2, U7R.8 (VDD), U8H.8 (VDD)
unnamed: J9.1, K_RES_H.1 (O), OUT_H.1
unnamed: K_RES_H.9 (2), RES_H.2
unnamed: LED8.K (C), R12.1
unnamed: LED9.K (C), R13.1
unnamed: LED10.K (C), R14.1
unnamed: LED11.K (C), R15.1
unnamed: LED12.K (C), R16.1
unnamed: LED13.K (C), R17.1
unnamed: ABC.4, ABC3.1, ABC4.1, J7.4, NWS2.2, WS4.1
OB1: IC1.10 (O7), K1_CD.16 (2), K2_CD.16 (2), K3_C.2 (1), R14.2
OB2: IC2.10 (O7), K1_EF.15 (4), K4_F.2 (1), R13.2, RES_H.1
OG1: IC1.12 (O5), K1_AB.15 (4), K4_B.2 (1), MONO3.2, R17.2
OG2: IC2.12 (O5), K1_EF.16 (2), K2_EF.16 (2), K3_E.2 (1), MONO3.1, R12.2
OR1: IC1.14 (O3), K1_AB.16 (2), K2_AB.16 (2), K3_A.2 (1), R16.2
OR2: IC2.14 (O3), K1_CD.15 (4), K4_D.2 (1), R15.2

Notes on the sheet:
4-pol oder 6-pol Wannenstecker
Optional WS2811 SMD
Zur nächsten Platine. Über diesen Stecker können mehrere Platinen miteinander verbunden werden. Dadurch benötigt man nur einen Anschluss zur Verteilerplatine. Hier können U-Förmige Verbinder verwendet werden: https://www.elektronikpraxis.vogel.de/stiftleisten-fuer-planare-verbindung-a-413944/. Dumm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
Von vorangegangener Platine
Der WS2811 kann optional auch als SMD bestückt werden weil diese Version billiger und besser verfügbar ist.
Ver.: 1.0
Entweder C1H (Hubert) oder C1R (Rolf) bestücken
Jumper TERM schließen wenn keine weiteren Platinen an Stecker SV3 angeschlossen werden.
Revision History: 08.05.20: Started
Vorabschnitt
ABC Bremsen
Not-Halt
Wenn nur 3 Monostbile Relais verwendet werden, dann werden nur die unteren IC's Bestückt (WS2811 und ULN2003) und der Jumper MONO3 und SINGLE verbunden.
- Herzstückpolarisation - ABC Bremsen Varianten: 3 bistabile Relais 2x um (HFD2-L 5V) 3 norm. Relais 2x um (HFD2 5V/G5V-2 5DC) 6 norm. Relais 1x um (G5V-1 5V) 2 optionale Relais 1x um (G5V-1 5V)
Auf der Platine war noch Platz. Darum wurden noch zwei optionale WS2811 vorgesehen. Wenn diese nicht bestückt werden. dann müssen die Jumper NO_OPTW1 und NO_OPTW2 geschlossen werden. Es kann entwerder das LED K_RES oder die LED an Pin 8 von des Steckers OPT_LED benutzt werden.
Com
Achtung: Mit der Platine dürfen keine Spannungen größer als 50V geschaltet werden weil die Abstände der Leiterbahnen zu gering sind!
Maximaler Schaltstrom: 1A bei 1x um Relas 2A bei 2x um Relais Power Leiterbahnen mind. 24mil => 2A @20°C dT
https://www.multi-circuit-boards.eu/leiterplatten-design-hilfe/oberflaeche/leiterbahn-strombelastbarkeit.html

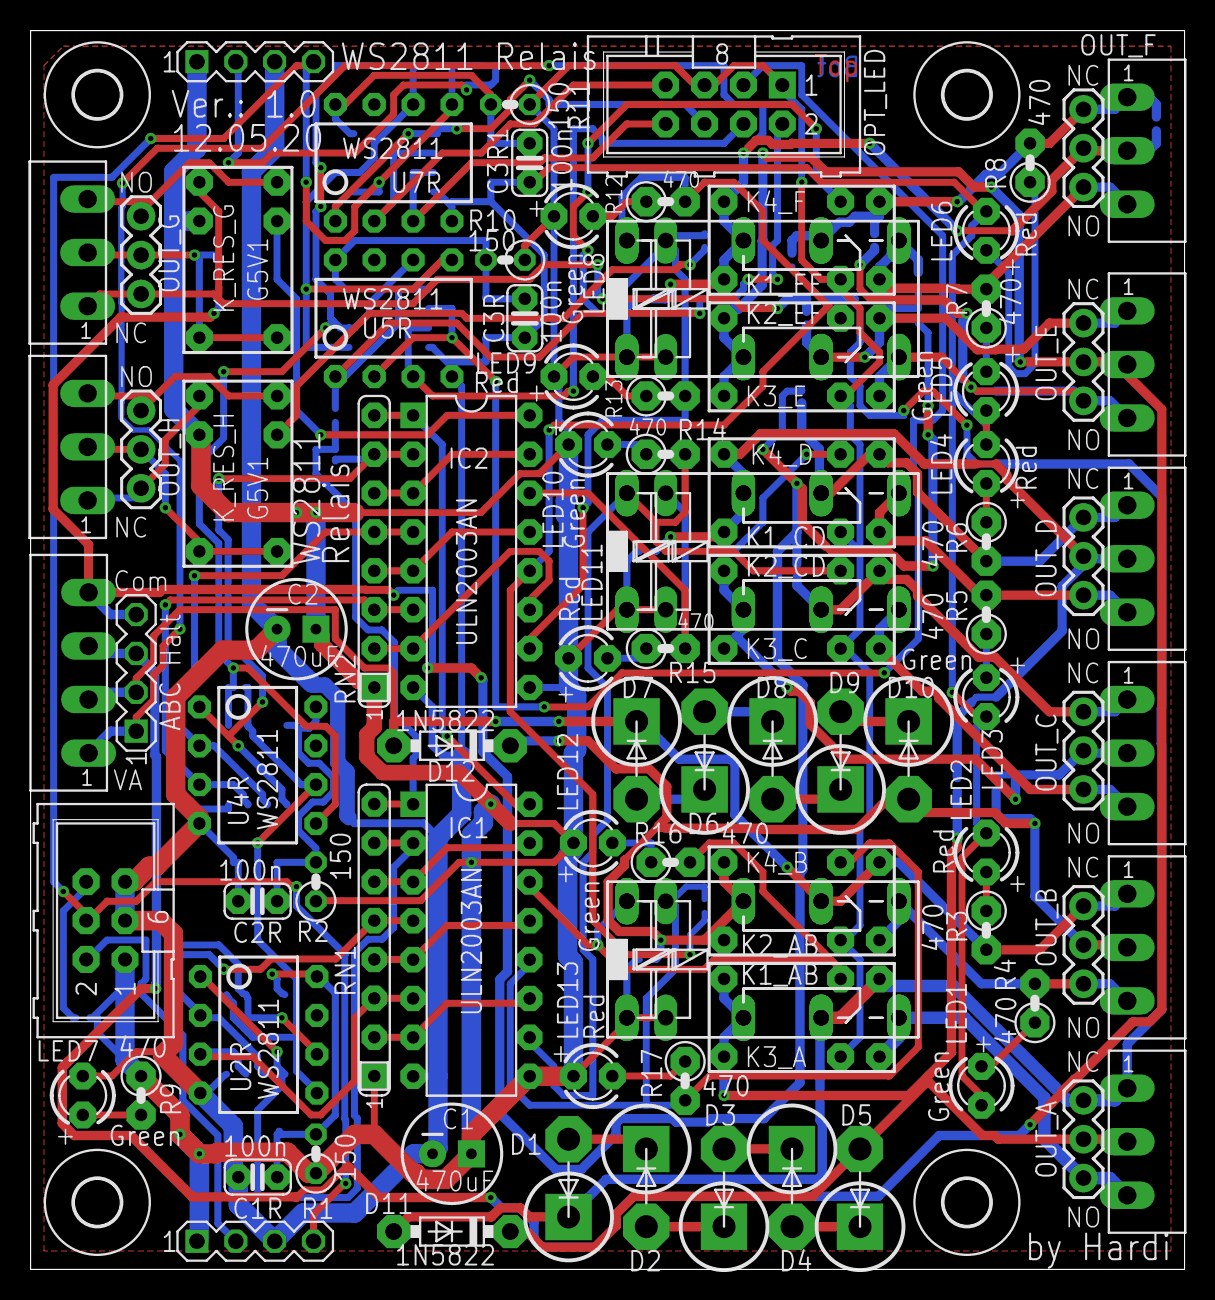
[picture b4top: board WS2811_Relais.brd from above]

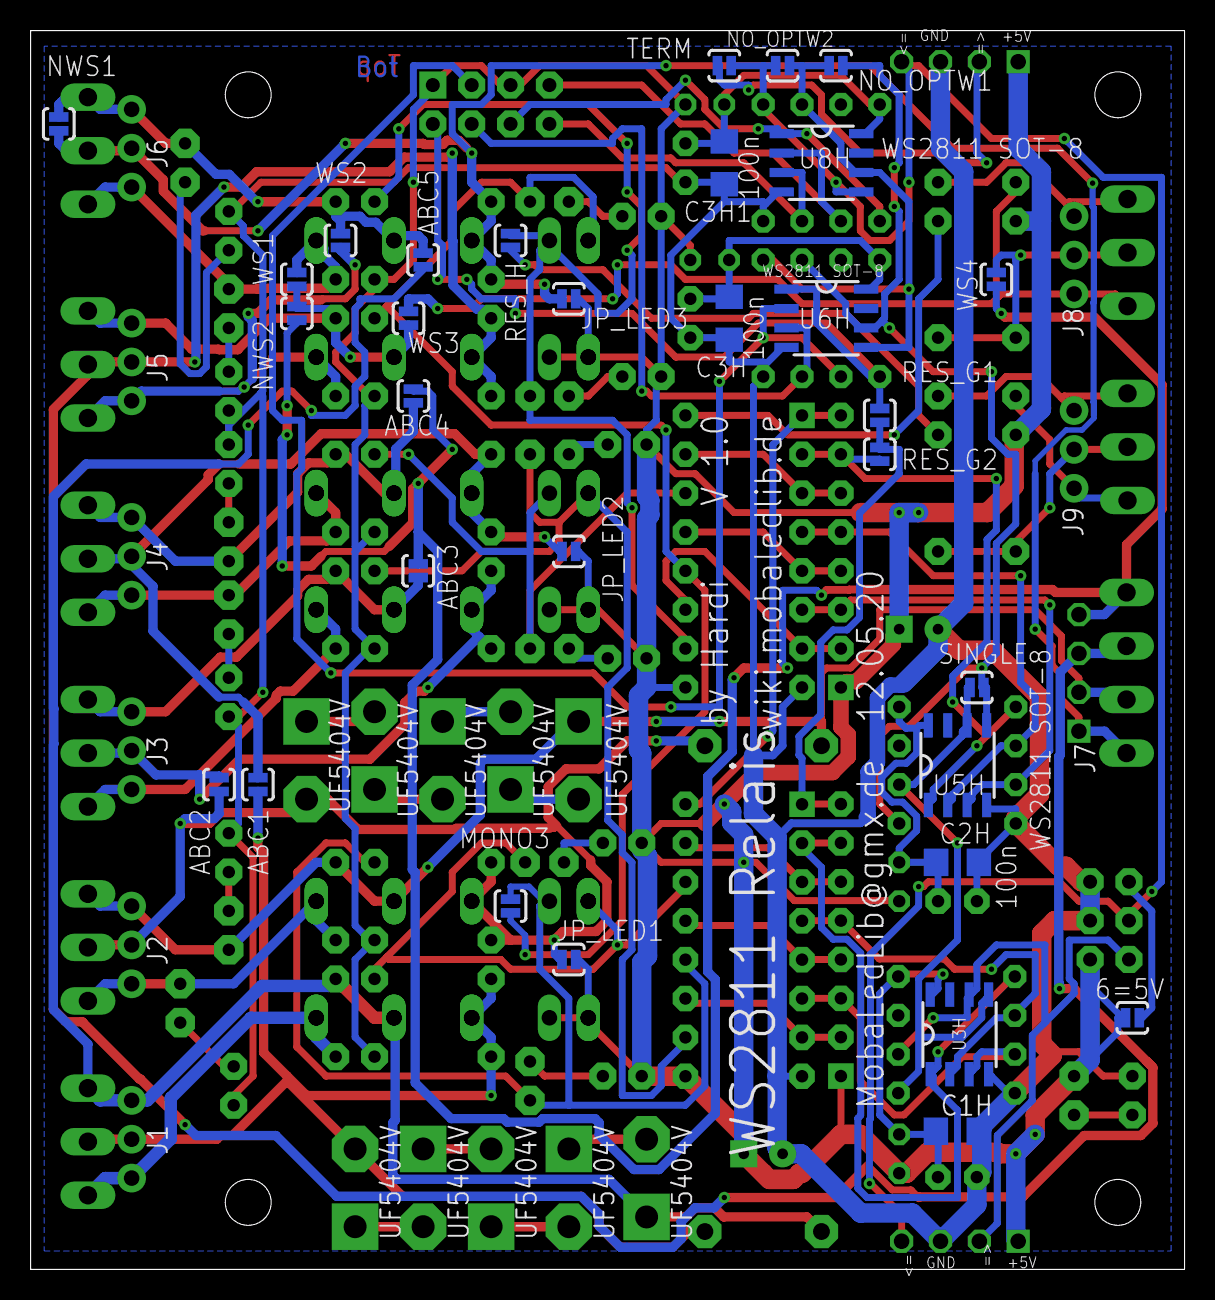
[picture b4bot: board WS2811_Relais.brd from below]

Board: 2 copper layers, 75.4 x 81.0 mm, 127 parts (31 on the bottom side), 87 nets.
